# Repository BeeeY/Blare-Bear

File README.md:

# Blare-Bear
A bear shaped alarm clock :3

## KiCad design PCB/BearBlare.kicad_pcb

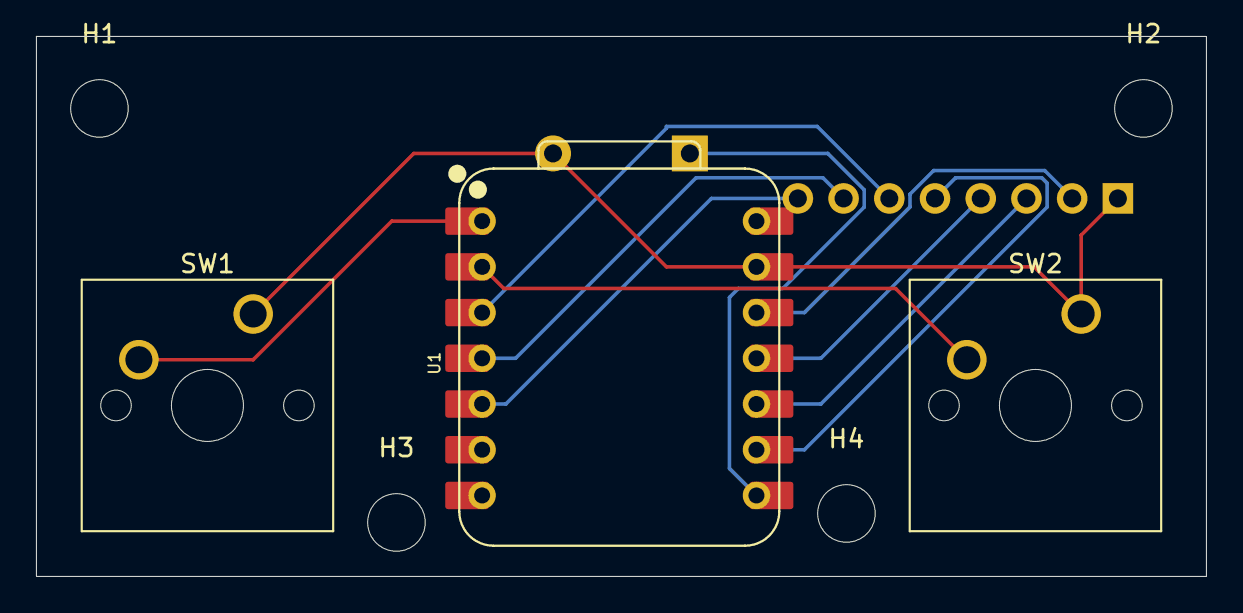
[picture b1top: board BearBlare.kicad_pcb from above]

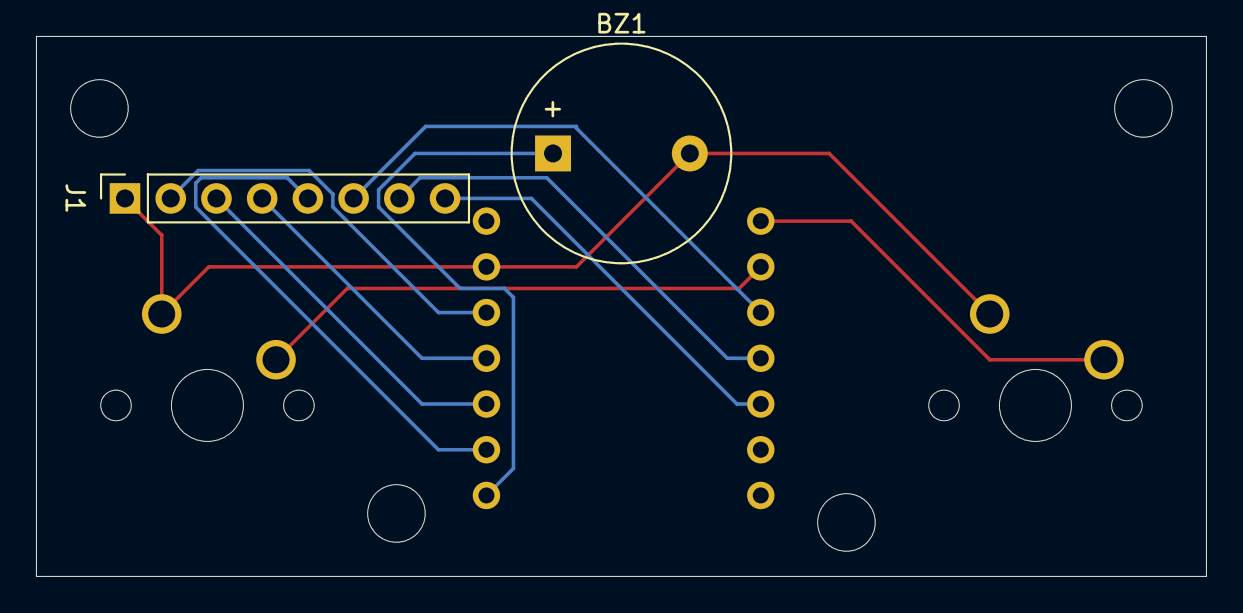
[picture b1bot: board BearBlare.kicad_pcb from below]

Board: 2 copper layers, 65.0 x 30.0 mm, 9 parts (2 on the bottom side), 11 nets.

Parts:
BZ1: Buzzer; Buzzer_12x9.5RM7.6
H1, H2, H3, H4: MountingHole; MountingHole_3.2mm_M3
J1: Conn_01x08_Pin; PinSocket_1x08_P2.54mm_Vertical
SW1, SW2: SW_Push; SW_Cherry_MX_1.00u_PCB
U1: XIAO-ESP32-C3-SMD; XIAO-ESP32-C3-DIP

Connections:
+3.3V: J1.2, U1.12 (3V3_OUT)
/BL: J1.8, U1.5 (D4)
/CS: J1.7, U1.4 (D3)
/DC: J1.6, U1.3 (D2)
/RST: J1.5, U1.9 (D8)
/SCL: J1.3, U1.10 (D9/BOOT)
/SDA: J1.4, U1.11 (D10)
GND: BZ1.2 (-), J1.1, SW1.1, SW2.1, U1.13 (GND)
unnamed: BZ1.1 (+), U1.8 (D7)
unnamed: SW1.2, U1.1 (D0)
unnamed: SW2.2, U1.2 (D1)
